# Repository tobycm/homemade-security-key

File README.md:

# homemade-security-key

DIY a security key! powered by a rp2350 for a pretty good security :D

with a nice 3d printed case and it is also easy to print, this key is hella nice for only 6$ each 🔥

the pcb is still well made tho, considerate thoughts have been put into the usb routing, and power delivery too!

## 3D Render

### PCB

### Case

| Type | Qty | Value |
| :--- | :-- | :--- |
| Capacitor | 1 | 10u |
| Capacitor | 10 | 100n |
| Capacitor | 1 | 1u |
| Capacitor | 1 | 22u |
| Capacitor | 4 | 4.7u |
| Capacitor | 2 | 18p |
| LED | 1 | B38G3RGB-10D0003H2U1930 |
| Connector | 1 | UP20-C-F-G-FL-1-P12-TR |
| Connector | 1 | UP2-AH-1-TH |
| Inductor | 1 | 4.7u |
| Inductor | 1 | AOTA-B201610S3R3-101-T |
| Resistor | 1 | 5.1k |
| Resistor | 2 | 27 |
| Resistor | 1 | 1k |
| Resistor | 1 | 10k |
| Resistor | 1 | 147 |
| Resistor | 3 | 33 |
| Button | 1 | PTS526SM15SMTR2 LFS |
| Buck regulator | 1 | AP63203WU-7 |
| Flash | 1 | W25Q16JVSS |
| MCU | 1 | RP2350A-QFN60 |
| Crystal | 1 | ABM8-272-T3 |
| PCB | 1 | |
| Stencil | 1 | |
| Solder paste | 1 | I already have |

---
**Total cost:** $64.78 USD

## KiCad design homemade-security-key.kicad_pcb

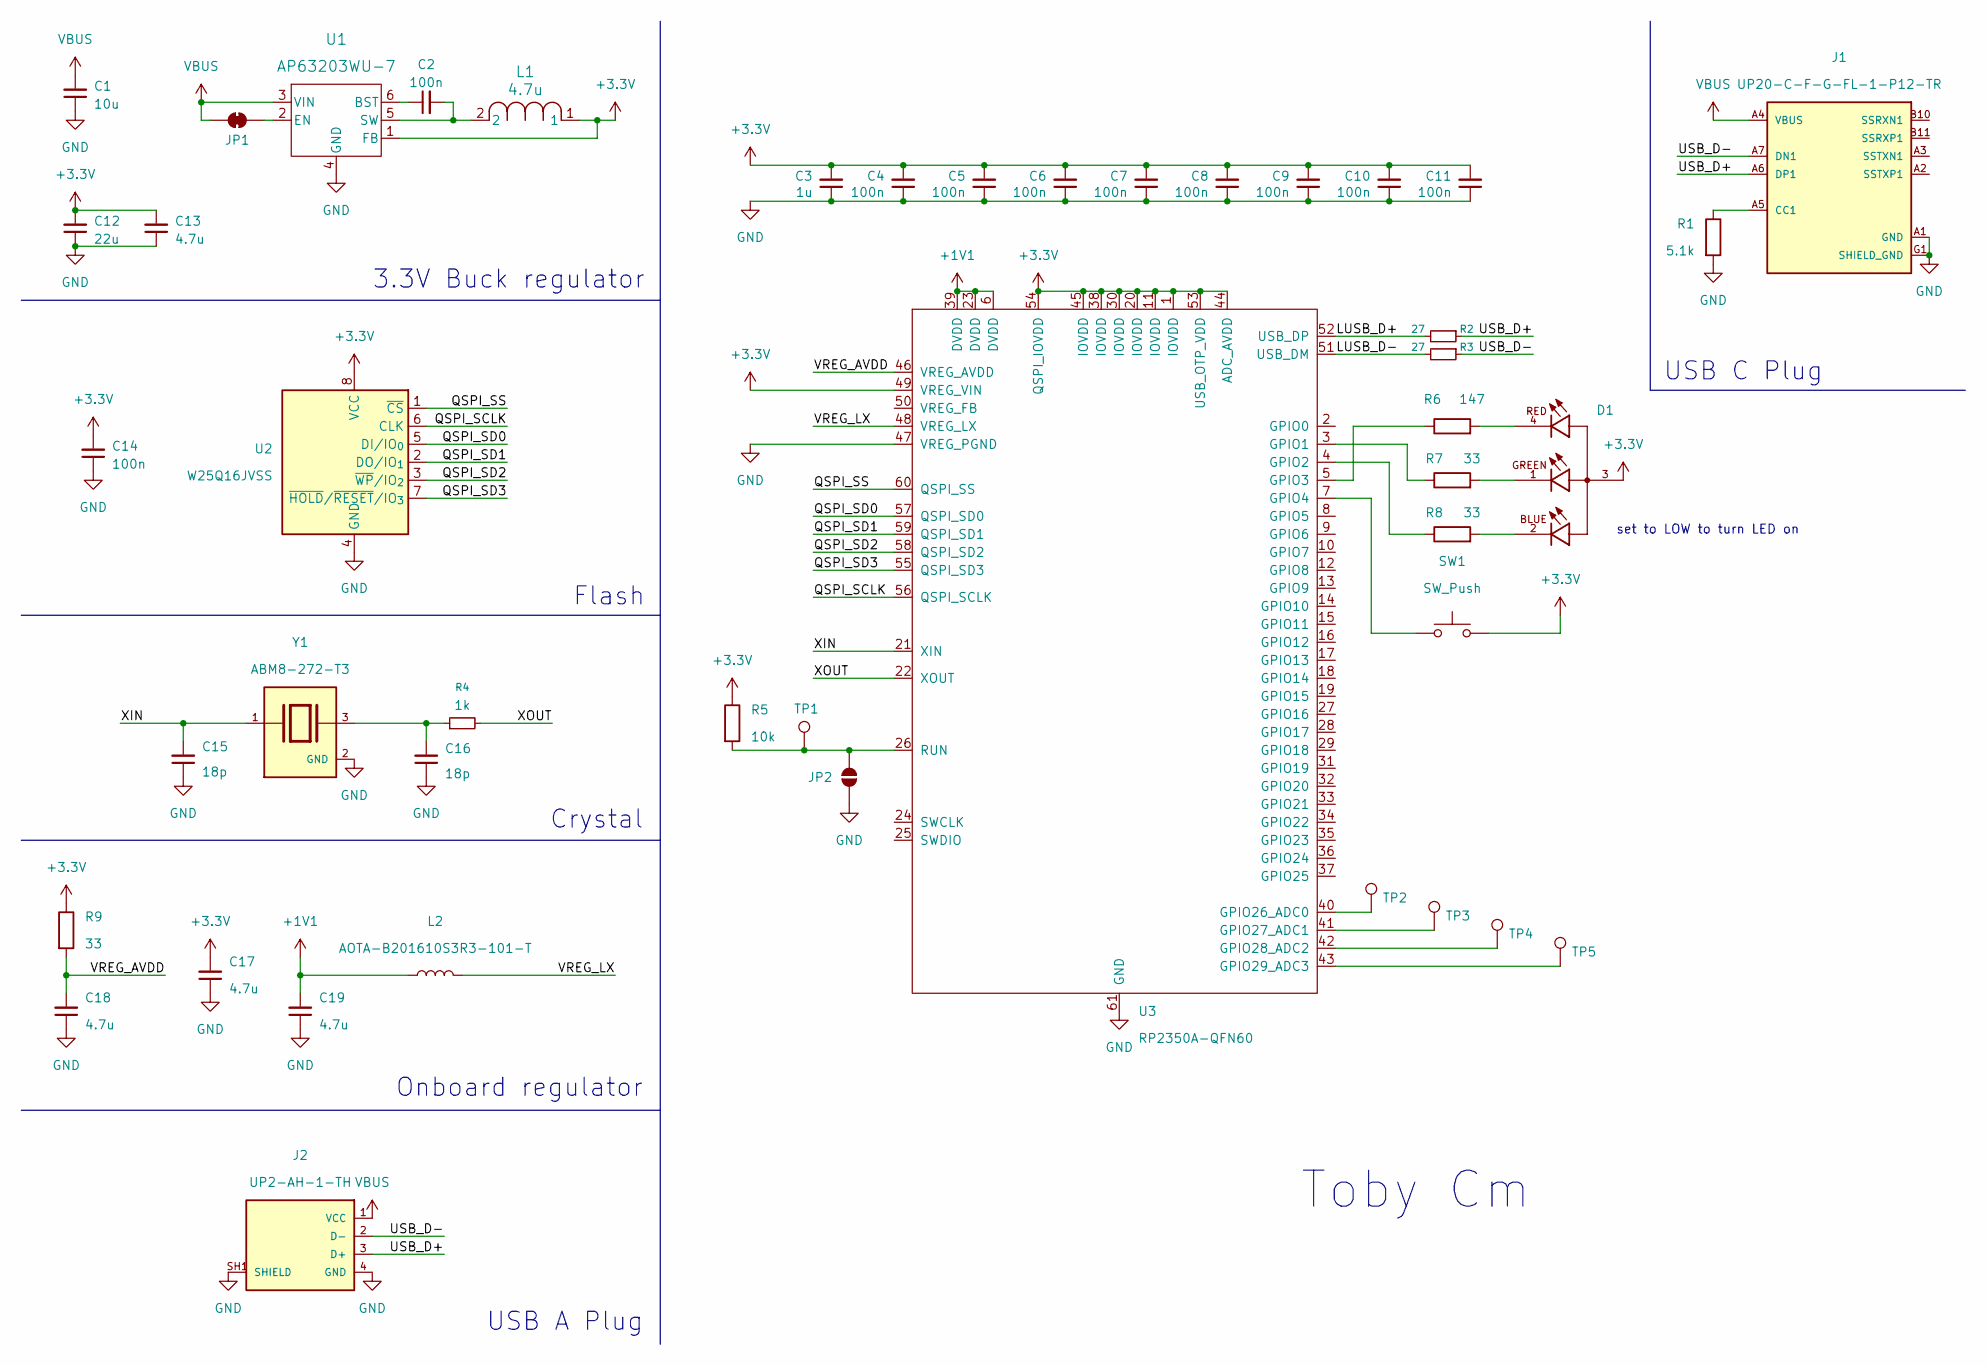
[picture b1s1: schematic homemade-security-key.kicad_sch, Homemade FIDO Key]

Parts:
C1: 10u; C_0805_2012Metric
C2, C4, C5, C6, C7, C8, C9, C10, C11, C14: 100n; C_0402_1005Metric
C3: 1u; C_0402_1005Metric
C12: 22u; C_0603_1608Metric
C13, C17, C18, C19: 4.7u; C_0402_1005Metric
C15, C16: 18p; C_0402_1005Metric
D1: B38G3RGB-10D0003H2U1930; LED_B38G3RGB-10D0003H2U1930; PARTREV 1.9
J1: UP20-C-F-G-FL-1-P12-TR; SAMESKY_UP20-C-F-G-FL-1-P12-TR; PARTREV 1.0
J2: UP2-AH-1-TH; CUI_UP2-AH-1-TH; PARTREV 1.05
JP1: SolderJumper_2_Bridged; SolderJumper-2_P1.3mm_Bridged_RoundedPad1.0x1.5mm
JP2: SolderJumper_2_Open; SolderJumper-2_P1.3mm_Open_RoundedPad1.0x1.5mm
L1: 4.7u; IND_HPC6045NC_TTA
L2: AOTA-B201610S3R3-101-T; L_0805_2012Metric_Pad1.15x1.40mm_HandSolder
R1: 5.1k; R_0402_1005Metric
R2, R3: 27; R_0402_1005Metric
R4: 1k; R_0402_1005Metric
R5: 10k; R_0402_1005Metric
R6: 147; R_0402_1005Metric
R7, R8, R9: 33; R_0402_1005Metric
SW1: SW_Push; SON4_PTS526 SM15 SMTR2 LFS_CNK
TP1, TP2, TP3, TP4, TP5: TestPoint; TestPoint_Pad_D2.0mm
U1: AP63203WU-7; AP63203WU-7_DIO
U2: W25Q16JVSS; SOIC-8_5.3x5.3mm_P1.27mm
U3: RP2350A-QFN60; RP2350A_QFN-60_EP_7.75x7.75_Pitch0.4mm
Y1: ABM8-272-T3; XTAL_ABM8-272-T3; PARTREV 07-29-20

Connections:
+1V1: C19.2, L2.1, U3.6 (DVDD), U3.23 (DVDD), U3.39 (DVDD)
+3.3V: C3.2, C4.2, C5.2, C6.2, C7.2, C8.2, C9.2, C10.2, C11.2, C12.2, C13.2, C14.2, C17.2, D1.3, L1.1, R5.1, R9.1, SW1.3, SW1.4, U1.1 (FB), U2.8 (VCC), U3.1 (IOVDD), U3.11 (IOVDD), U3.20 (IOVDD), U3.30 (IOVDD), U3.38 (IOVDD), U3.44 (ADC_AVDD), U3.45 (IOVDD), U3.49 (VREG_VIN), U3.53 (USB_OTP_VDD), U3.54 (QSPI_IOVDD)
/LUSB_D+: R2.2, U3.52 (USB_DP)
/LUSB_D-: R3.2, U3.51 (USB_DM)
/QSPI_SCLK: U2.6 (CLK), U3.56 (QSPI_SCLK)
/QSPI_SD0: U2.5 (DI/IO_{0}), U3.57 (QSPI_SD0)
/QSPI_SD1: U2.2 (DO/IO_{1}), U3.59 (QSPI_SD1)
/QSPI_SD2: U2.3 (~WP/IO_{2}), U3.58 (QSPI_SD2)
/QSPI_SD3: U2.7 (~HOLD/~RESET/IO_{3}), U3.55 (QSPI_SD3)
/QSPI_SS: U2.1 (~CS), U3.60 (QSPI_SS)
/USB_D+: J1.A6 (DP1), J2.3 (D+), R2.1
/USB_D-: J1.A7 (DN1), J2.2 (D-), R3.1
/VREG_AVDD: C18.2, R9.2, U3.46 (VREG_AVDD)
/VREG_LX: L2.2, U3.48 (VREG_LX)
/XIN: C15.2, U3.21 (XIN), Y1.1
/XOUT: R4.2, U3.22 (XOUT)
GND: C1.1, C3.1, C4.1, C5.1, C6.1, C7.1, C8.1, C9.1, C10.1, C11.1, C12.1, C13.1, C14.1, C15.1, C16.1, C17.1, C18.1, C19.1, J1.A1 (GND), J1.A12 (GND__1), J1.B12 (GND__2), J1.G1 (SHIELD_GND), J1.G2 (SHIELD_GND__1), J1.G3 (SHIELD_GND__2), J1.G4 (SHIELD_GND__3), J2.4 (GND), J2.SH1 (SHIELD), J2.SH2 (SHIELD__1), JP2.1 (A), R1.2, U1.4 (GND), U2.4 (GND), U3.47 (VREG_PGND), U3.61 (GND), Y1.2 (GND), Y1.4 (GND)
unnamed: C16.2, R4.1, Y1.3
unnamed: D1.1, R7.2
unnamed: D1.2, R8.2
unnamed: D1.4, R6.2
unnamed: J1.A5 (CC1), R1.1
unnamed: JP1.2 (B), U1.2 (EN)
unnamed: JP2.2 (B), R5.2, TP1.1, U3.26 (RUN)
unnamed: C2.1, U1.6 (BST)
unnamed: C2.2, L1.2, U1.5 (SW)
unnamed: R7.1, U3.3 (GPIO1)
unnamed: R8.1, U3.4 (GPIO2)
unnamed: R6.1, U3.5 (GPIO3)
unnamed: SW1.1, SW1.2, U3.7 (GPIO4)
unnamed: TP2.1, U3.40 (GPIO26_ADC0)
unnamed: TP3.1, U3.41 (GPIO27_ADC1)
unnamed: TP4.1, U3.42 (GPIO28_ADC2)
unnamed: TP5.1, U3.43 (GPIO29_ADC3)
VBUS: C1.2, J1.A4 (VBUS), J1.B9 (VBUS__1), J2.1 (VCC), JP1.1 (A), U1.3 (VIN)

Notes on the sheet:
Toby Cm
Flash
Crystal
Onboard regulator
set to LOW to turn LED on
3.3V Buck regulator
USB C Plug
USB A Plug

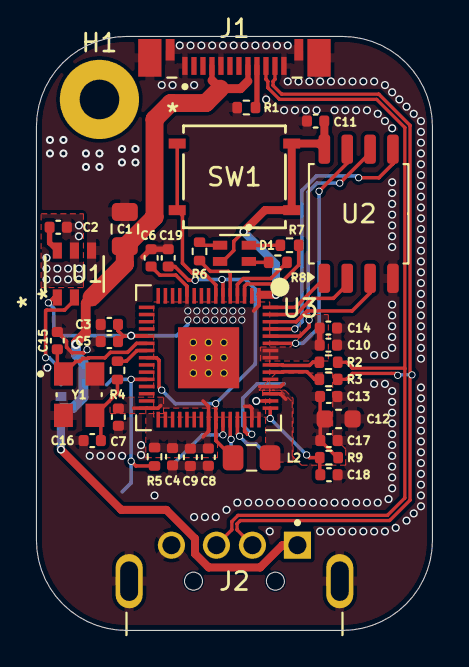
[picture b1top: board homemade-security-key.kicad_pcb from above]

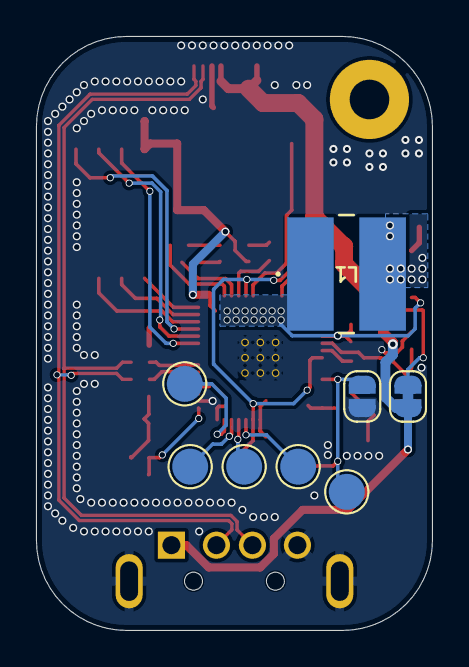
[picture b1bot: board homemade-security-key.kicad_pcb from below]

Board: 2 copper layers, 22.0 x 33.0 mm, 46 parts (8 on the bottom side), 35 nets.

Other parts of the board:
H1: MountingHole; MountingHole_2.2mm_M2_Pad

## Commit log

2025-07-27 init
2025-07-31 pcb done!
2025-08-01 journal and readme done!!
2025-08-01 add 3d files
2025-08-01 add total hours
2025-08-01 add bom
2025-08-01 final push hehe
2025-08-01 add bom because git ignored it :skull:
2026-04-25 add gerbers
